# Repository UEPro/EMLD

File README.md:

# EMLD
Electromagnetic Listening Device<br />

This PCB was designed for a Workshop in Germany, thus the documentation is in German. Contact me if you need a translation (Contact info in folder "Documentation", file "Anleitung_EMLD")

<b>AKF-WORKSHOP:</b></n>

Hallo ihr Lieben, ich hoffe ihr hattet alle ein tolles Festival und seid gut Heim gekommen. :)

Vielen Dank, dass ihr beim Workshop mitgemacht habt. Es hat mir riesigen Spaß gemacht, mit euch zu Arbeiten und ich hoffe auch ihr hattet Freude am basteln.

Dieses Archiv ist noch ziemlich leer, ich werde es aber diese Woche füllen. Wenn ihr ab Montag wieder kommt, sollte alles hier sein.

Solltet ihr irgendwelche Fragen oder Probleme haben, schreibt mir einfach über github oder schickt mir eine E-Mail (die Adresse steht in der Anleitung oben im Ordner "Documentation").

Ich werde außerdem eine Facebookseite einrichten, damit ihr mich einfacher kontaktieren könnt. Der Link dazu kommt dann hier her.

Schreibt mir gerne auch für weiteres Feedback und Vorschläge.

Nochmals Danke für die tolle Zeit mit euch und das nette Feedback :) Ich hoffe man sieht sich wieder.

Downloadanleitung:<br />
-Einzelne Datei: Rechtsklick auf die Datei → "Ziel speichern unter" anklicken<br />
-Ganzes Archiv: oben rechts den grünen Knopf "Clone or download" anklicken → "Download as ZIP" anklicken → ZIP Archiv entpacken

This project is based on LOM-Instrument's <a href="https://github.com/LOM-instruments/Elektrosluch-3">Electrosluch-3</a> and was adapted for the AKF festival's synthesizer workshop.

<br /><span xmlns:dct="http://purl.org/dc/terms/" property="dct:title">Electromagnetic Listening Device</span> by <a xmlns:cc="http://creativecommons.org/ns#" href="https://github.com/UEPro/" property="cc:attributionName" rel="cc:attributionURL">Useless Electronics Projects</a> is licensed under a <a rel="license" href="http://creativecommons.org/licenses/by-sa/4.0/">Creative Commons Attribution-ShareAlike 4.0 International License</a>.<br />

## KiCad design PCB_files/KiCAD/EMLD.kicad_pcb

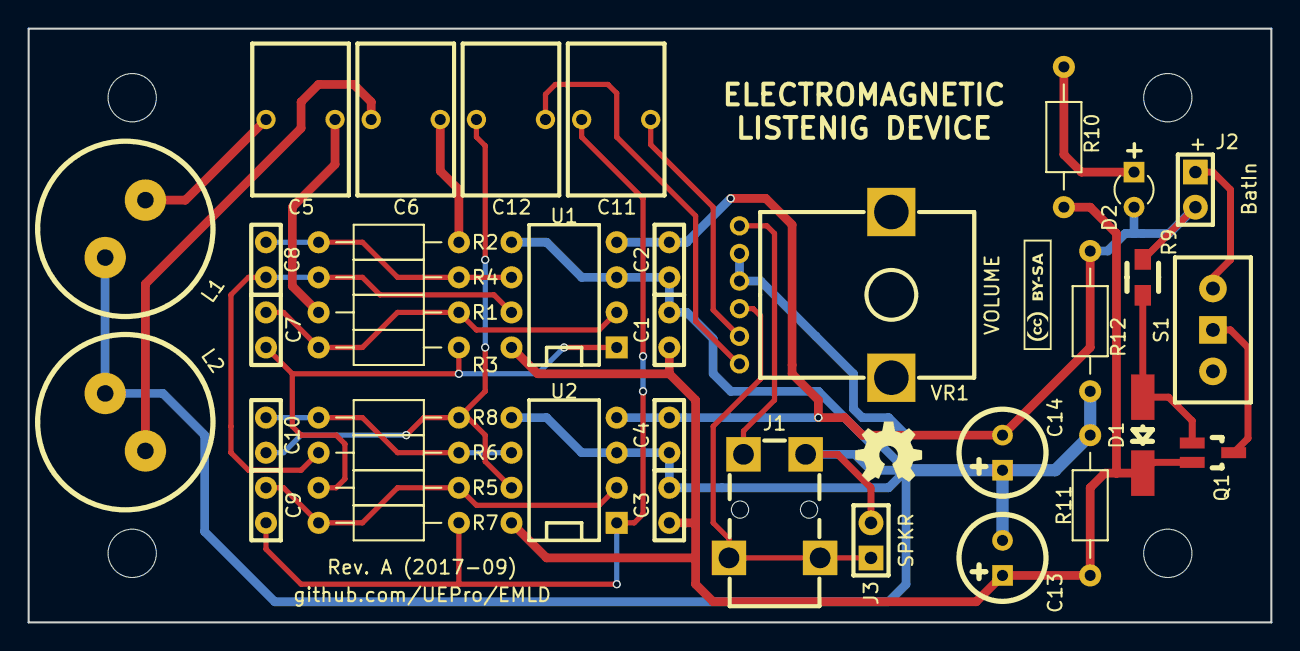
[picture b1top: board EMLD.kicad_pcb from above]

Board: 2 copper layers, 90.0 x 43.0 mm, 44 parts (0 on the bottom side), 23 nets.

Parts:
C1, C2, C3, C4: 100n; C_rect-radial-bipolar-100mil-2x5mm
C5, C6, C11, C12: 2µ2; C-Rect_L7_W11_P5
C7, C8, C9, C10: 47p; C_rect-radial-bipolar-100mil-2x5mm
C13, C14: 220µ/16V; C_round-radial-polar-2,5mm-6,3mm
D1: 3V; Diode_MiniMELF-Handsoldering
D2: 3mm/cyan; LED_2pin-3mm
Des*: Val*; MountingHole-3,5mm
Des*#2, Des*#3, Des*#4: Val*; MountingHole-3,5mm
J1: Klinke-stereo; Lumberg-1503-07-Klinke-3,5mm
J2: BatIn; PinArray-100mil-1x2
J3: Val*; PinArray-100mil-1x2
L1, L2: 22mH; C_round-radial-bipolar-5mm-12,5mm
Q1: FDN304; SOT23-Handsoldering
R1, R2, R5, R6: 1k; R_axial_400mil
R3, R4, R7, R8: 120k; R_axial_400mil
R9: 100k; SMD0805-HandSoldering
R10: 10k; R_axial_400mil
R11, R12: 100k; R_axial_400mil
S1: S_1P2T; S-Schiebeschalter_China_SPDT
U1, U2: NE5532; DIP-8_300
VAL: REF; CC-BY-SA_08mm_Fsi
VAL#2: REF; oshw5mm
VR1: 10k log; VR-Alps_R12L_vert

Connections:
+4V5: C1.2, C2.1, C3.2, C4.1, C13.2, C14.1, J1.1, J3.2, L1.2, L2.1, R11.2, R12.1, U1.3, U1.5, U2.3, U2.5, VR1.1, VR1.4
+9V: C1.1, C3.1, C13.1, D1.2, Q1.2, R10.1, R11.1, U1.8, U2.8
GND: C2.2, C4.2, C14.2, D2.2, J2.2, R9.2, R12.2, U1.4, U2.4
unnamed: C5.1, L1.1
unnamed: C5.2, R1.1
unnamed: C6.1, L2.2
unnamed: C6.2, R2.1
unnamed: C7.1, R1.2, R3.1, U1.2
unnamed: C7.2, R3.2, R5.1, U1.1
unnamed: C8.1, R2.2, R4.1, U1.6
unnamed: C8.2, R4.2, R6.1, U1.7
unnamed: C9.1, R5.2, R7.1, U2.2
unnamed: C10.1, R6.2, R8.1, U2.6
unnamed: C10.2, C12.1, R8.2, U2.7
unnamed: C9.2, C11.1, R7.2, U2.1
unnamed: C11.2, VR1.3
unnamed: C12.2, VR1.6
unnamed: D1.1, Q1.1, R9.1
unnamed: D2.1, R10.2
unnamed: J1.2, VR1.5
unnamed: J1.3, J3.1, VR1.2
unnamed: J2.1, S1.3
unnamed: Q1.3, S1.2
